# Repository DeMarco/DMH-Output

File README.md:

# DMH-Output
Kosmo format output module

## Features

### Line outputs and main volume

The L and R inputs accept the usual (Eurorack) modular synth audio amplitude of 10 V peak-to-peak.
The line level L and R outputs accept both balanced TRS and unbalanced TS cables.
The main volume control affects both L and R channels. The reduction factor can be set from from -infinite (silence) to -3 dB (max).
Since the usual 10 Vpp amplitude corresponds to around +13 dBu, this means the module can output from -infinite up to +10 dBu.
The precision dBu meter will max out at +6 dBu (red LED). Most professional audio equipment like mixers and audio interfaces expect a nominal input line level of +4 dBu.

### Headphone output

There's a separate stereo (TRS) headphone driving output with its own volume control, also with a range of -infinite to +10 dBu.
It can drive headphones with 32ohms or 85ohms with no problem. Higher impedances are also probably fine.

### External instrument inputs

The external inputs can amplify line level signals to the usual Eurorack amplitude of 10 Vpp with the help of a dedicated volume control. The input metering LEDs will turn yellow when the amplified signals at the Euro L and R outputs is between 9 and 11 Vpp, and red when above 11 Vpp.
This pre-amp has been designed with line level signals in mind, like those coming from another synthesizer or professional audio equipment. High impedance instrument outputs like electric guitars might not produce the best sound when connected directly to this module.

## Current consumption

+12V --> 110mA

-12V --> 110mA

## Dimensions

Height: 20cm

Width: 5cm

Depth: 5cm

## PCB set

- Front Panel
- Controls
- LEDs Aligner
- Main
- Mezzanine

## Gerbers

https://github.com/DeMarco/DMH-Output/tree/main/Gerbers

## Schematic and BoM

https://github.com/DeMarco/DMH-Output/blob/main/DMH_Output_Schematic.pdf

https://github.com/DeMarco/DMH-Output/blob/main/DMH_Output_BoM.csv

## Assembly and Calibration Instructions

https://github.com/DeMarco/DMH-Output/blob/main/Assembly_Instructions.md

## Font

For viewing/customizing in KiCad, I recommend downloading and installing the Nulshock font from Typodermic: https://typodermicfonts.com/nulshock/

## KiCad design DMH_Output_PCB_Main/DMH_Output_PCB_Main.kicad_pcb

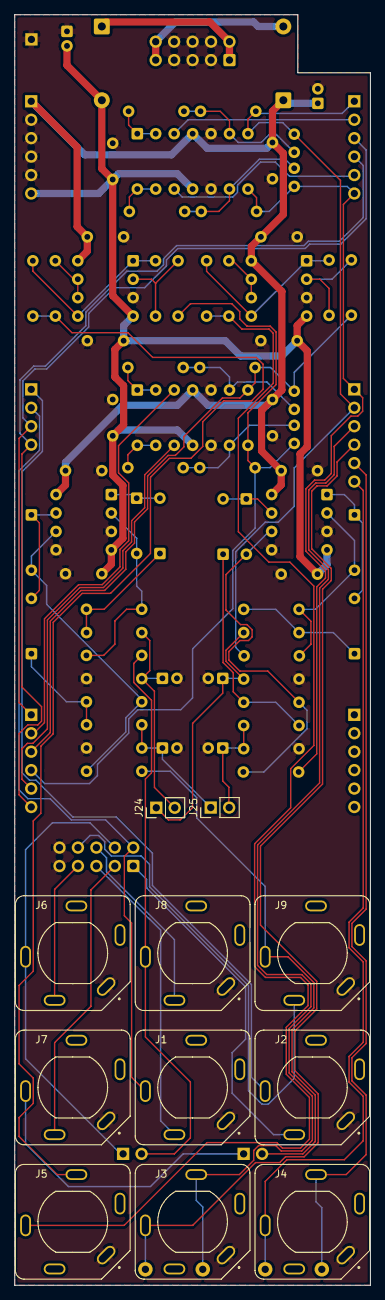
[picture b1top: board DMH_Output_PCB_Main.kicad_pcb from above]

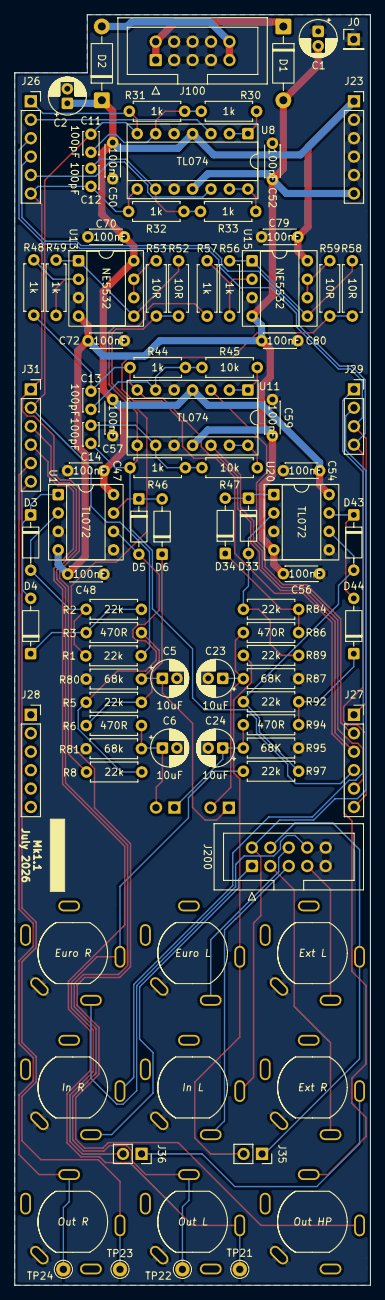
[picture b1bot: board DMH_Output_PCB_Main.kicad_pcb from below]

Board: 2 copper layers, 49.0 x 175.0 mm, 96 parts (85 on the bottom side), 63 nets.

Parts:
C1, C2: 47uF; CP_Radial_D5.0mm_P2.00mm
C5, C6, C23, C24: 10uF; CP_Radial_D5.0mm_P2.00mm
C11, C12, C13, C14: 100pF; C_Disc_D3.0mm_W2.0mm_P2.50mm
C47, C48, C50, C52, C54, C56, C57, C59, C70, C72, C79, C80: 100nF; C_Disc_D4.3mm_W1.9mm_P5.00mm
D1, D2: SB140; D_DO-41_SOD81_P10.16mm_Horizontal
D3, D4, D5, D6, D33, D34, D43, D44: 1N4148; D_DO-35_SOD27_P7.62mm_Horizontal
J0: Conn_01x01; PinHeader_1x01_P2.54mm_Vertical
J1, J2, J3, J4, J5, J6, J7, J8, J9: TRS_Jack_6.35mm_Sw; CUI_SJ-63083D
J23, J28: Conn_01x06; PinSocket_1x06_P2.54mm_Vertical
J24, J25: Conn_01x02; PinHeader_1x02_P2.54mm_Vertical
J26, J27, J31: Conn_01x06_PinHeader; PinSocket_1x06_P2.54mm_Vertical
J29: Conn_01x04_PinHeader; PinSocket_1x04_P2.54mm_Vertical
J35, J36: Conn_01x02_PinHeader; PinSocket_1x02_P2.54mm_Vertical
J100: IDC_02x05; IDC-Header_2x05_P2.54mm_Vertical_Eurorack
J200: IDC_02x05; IDC-Header_2x05_P2.54mm_Vertical_BackBone
R1, R2, R5, R8, R84, R89, R92, R97: 22k; R_Axial_DIN0207_L6.3mm_D2.5mm_P7.62mm_Horizontal
R3, R6, R86, R94: 470R; R_Axial_DIN0207_L6.3mm_D2.5mm_P7.62mm_Horizontal
R30, R31, R32, R33, R44, R46, R48, R49, R56, R57: 1k; R_Axial_DIN0207_L6.3mm_D2.5mm_P7.62mm_Horizontal
R45, R47: 10k; R_Axial_DIN0207_L6.3mm_D2.5mm_P7.62mm_Horizontal
R52, R53, R58, R59: 10R; R_Axial_DIN0207_L6.3mm_D2.5mm_P7.62mm_Horizontal
R80, R81: 68k; R_Axial_DIN0207_L6.3mm_D2.5mm_P7.62mm_Horizontal
R87, R95: 68K; R_Axial_DIN0207_L6.3mm_D2.5mm_P7.62mm_Horizontal
TP21, TP22, TP23, TP24: TestPoint; Pin_D1.0mm_L10.0mm
U1, U20: TL072; DIP-8_W7.62mm_Socket
U8, U11: TL074; DIP-14_W7.62mm_Socket
U13, U15: NE5532; DIP-8_W7.62mm_Socket

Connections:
+12V: C2.1, C47.1, C50.1, C54.1, C57.1, C70.1, C79.1, D2.1 (K), J23.1, U1.8 (V+), U8.4 (V+), U11.4 (V+), U13.8 (V+), U15.8 (V+), U20.8 (V+)
-12V: C1.2, C48.2, C52.2, C56.2, C59.2, C72.2, C80.2, D1.2 (A), J23.6, U1.4 (V-), U8.11 (V-), U11.11 (V-), U13.4 (V-), U15.4 (V-), U20.4 (V-)
/Balanced Line Driver/L_Bal_OUT_N_M: J3.R (4), J31.3, TP22.1 (1_1)
/Balanced Line Driver/L_Bal_OUT_P_M: J3.T (3), J31.4, TP21.1 (1_1)
/Balanced Line Driver/L_Ch_OUT_M: C11.2, J26.1, J31.2, R1.1, R31.2, U8.7
/Balanced Line Driver/R_Bal_OUT_N_M: J4.R (4), J31.5, TP24.1 (1_1)
/Balanced Line Driver/R_Bal_OUT_P_M: J4.T (3), J31.6, TP23.1 (1_1)
/Balanced Line Driver/R_Ch_OUT_M: C12.2, J26.6, J31.1, R8.1, R32.2, U8.8
/Gain Trimmer/L_Gain_IN_M: J26.3, J27.1, J29.3
/Gain Trimmer/R_Gain_IN_M: J26.4, J27.6, J29.4
/Headphone Amplifier/L_HP_OUT_M: J5.T (3), R52.2, R53.2
/Headphone Amplifier/R_HP_OUT_M: J5.R (4), R58.2, R59.2
/Input Meter/L_Ext_Meter_M: J8.T (3), J35.2, R89.1
/Input Meter/R_Ext_Meter_M: J9.T (3), J36.2, R97.1
/Pre-Gain Stage/L_In_M: J1.T (3), J29.2, J200.6
/Pre-Gain Stage/R_In_M: J2.T (3), J29.1
/PreAmp/L_Ext_IN_M: J6.T (3), J35.1, J200.7
/PreAmp/R_Ext_IN_M: J7.T (3), J36.1
GND: C1.1, C2.2, C5.2, C6.2, C23.2, C24.2, C47.2, C48.1, C50.2, C52.1, C54.2, C56.1, C57.2, C59.1, C70.2, C72.1, C79.2, C80.1, J0.1 (Pin_1_1), J1.S (1), J2.S (1), J3.S (1), J4.S (1), J5.S (1), J6.S (1), J7.S (1), J8.S (1), J9.S (1), J23.2, J23.3, J23.4, J23.5, J100.2a, J100.2b, J100.3a, J100.3b, J100.4a, J100.4b, J200.5, J200.10, R80.1, R81.1, R87.1, R95.1, U1.3 (+), U1.5 (+), U8.5 (+), U8.10 (+), U11.5 (+), U11.10 (+), U13.3 (+), U15.3 (+), U20.3 (+), U20.5 (+)
Input_Meter_L_M: C23.1, J24.2, R86.2, R87.2
Input_Meter_R_M: C24.1, J25.1, R94.2, R95.2
unnamed: D1.1 (K), J100.1a, J100.1b
unnamed: D2.2 (A), J100.5a, J100.5b
unnamed: D3.2 (A), R1.2, R2.1, U1.2 (-)
unnamed: D3.1 (K), D4.2 (A), U1.1
unnamed: D4.1 (K), R2.2, R3.1
unnamed: D5.2 (A), R5.1, R8.2, U1.6 (-)
unnamed: D5.1 (K), D6.2 (A), U1.7
unnamed: D6.1 (K), R5.2, R6.1
unnamed: D33.2 (A), R84.1, R89.2, U20.2 (-)
unnamed: D33.1 (K), D34.2 (A), U20.1
unnamed: D34.1 (K), R84.2, R86.1
unnamed: D43.2 (A), R92.1, R97.2, U20.6 (-)
unnamed: D43.1 (K), D44.2 (A), U20.7
unnamed: D44.1 (K), R92.2, R94.1
unnamed: J1.TN (2), J200.3
unnamed: J2.TN (2), J200.1
unnamed: J26.2, U8.3 (+)
unnamed: J26.5, U8.12 (+)
unnamed: J27.2, U11.3 (+)
unnamed: C13.2, J27.3, R44.2, R48.1, U11.7
unnamed: C14.2, J27.4, R46.2, R57.1, U11.8
unnamed: J27.5, U11.12 (+)
unnamed: J7.TN (2), J200.2
unnamed: J6.TN (2), J200.4
unnamed: J8.TN (2), J200.8
unnamed: J9.TN (2), J200.9
unnamed: R30.1, U8.1, U8.2 (-)
unnamed: C11.1, R30.2, R31.1, U8.6 (-)
unnamed: C12.1, R32.1, R33.2, U8.9 (-)
unnamed: R33.1, U8.13 (-), U8.14
unnamed: R45.1, U11.1, U11.2 (-)
unnamed: C13.1, R44.1, R45.2, U11.6 (-)
unnamed: C14.1, R46.1, R47.2, U11.9 (-)
unnamed: R47.1, U11.13 (-), U11.14
unnamed: R48.2, R49.1, U13.2 (-)
unnamed: R49.2, R52.1, U13.1, U13.5 (+)
unnamed: R53.1, U13.6 (-), U13.7
unnamed: R56.1, R57.2, U15.2 (-)
unnamed: R56.2, R58.1, U15.1, U15.5 (+)
unnamed: R59.1, U15.6 (-), U15.7
Output_Meter_L_M: C5.1, J24.1, R3.2, R80.2
Output_Meter_R_M: C6.1, J25.2, R6.2, R81.2

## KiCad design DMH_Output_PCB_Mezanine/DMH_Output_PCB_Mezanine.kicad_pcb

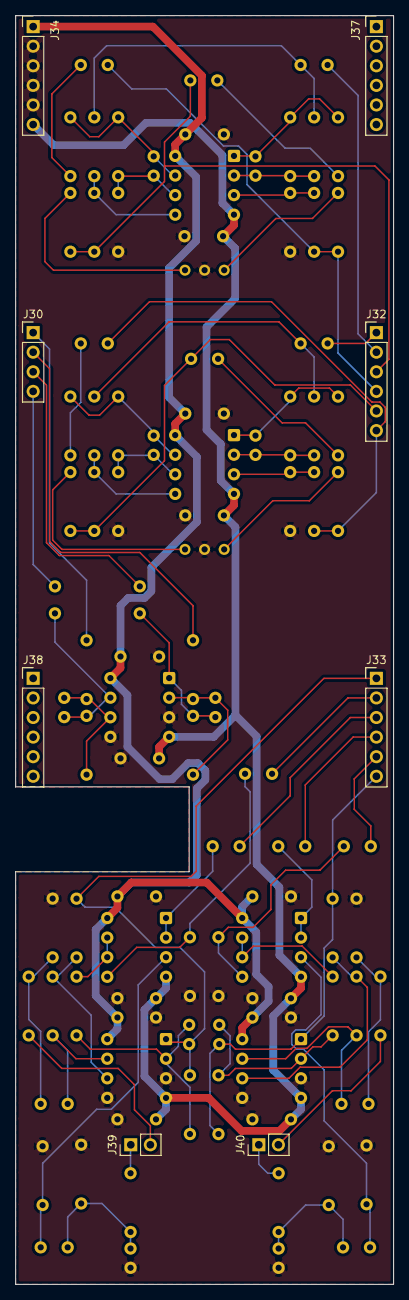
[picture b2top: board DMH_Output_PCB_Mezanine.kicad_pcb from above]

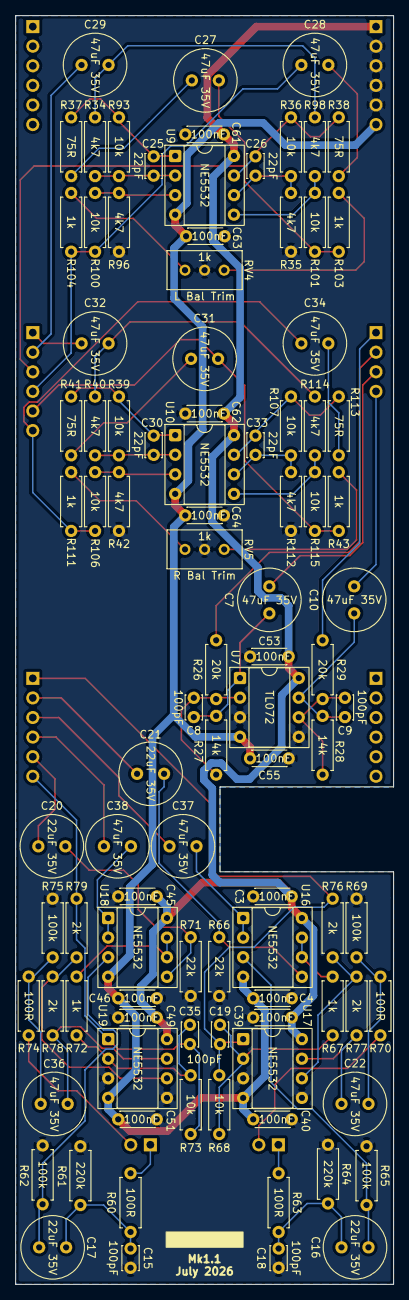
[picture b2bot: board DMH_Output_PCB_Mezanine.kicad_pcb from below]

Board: 2 copper layers, 49.0 x 164.5 mm, 105 parts (97 on the bottom side), 67 nets.

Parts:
C3, C4, C39, C40, C45, C46, C49, C51, C53, C55, C61, C62, C63, C64: 100nF; C_Disc_D4.3mm_W1.9mm_P5.00mm
C7, C10, C22, C27, C28, C29, C31, C32, C34, C36, C37, C38: 47uF 35V; C_Radial_D8.0mm_H11.5mm_P3.50mm
C8, C9, C15, C18, C19, C35: 100pF; C_Disc_D3.0mm_W2.0mm_P2.50mm
C16, C17, C20, C21: 22uF 35V; C_Radial_D8.0mm_H11.5mm_P3.50mm
C25, C26, C30, C33: 22pF; C_Disc_D3.0mm_W2.0mm_P2.50mm
J30: Conn_01x04_PinHeader; PinHeader_1x04_P2.54mm_Vertical
J32: Conn_01x06_PinHeader; PinHeader_1x06_P2.54mm_Vertical
J33, J34, J37, J38: Conn_01x06; PinHeader_1x06_P2.54mm_Vertical
J39, J40: Conn_01x02_PinHeader; PinHeader_1x02_P2.54mm_Vertical
R26, R29: 20k; R_Axial_DIN0207_L6.3mm_D2.5mm_P7.62mm_Horizontal
R27, R28: 14k; R_Axial_DIN0207_L6.3mm_D2.5mm_P7.62mm_Horizontal
R34, R35, R40, R42, R96, R98, R112, R114: 4k7; R_Axial_DIN0207_L6.3mm_D2.5mm_P7.62mm_Horizontal
R36, R39, R68, R73, R93, R100, R101, R106, R107, R115: 10k; R_Axial_DIN0207_L6.3mm_D2.5mm_P7.62mm_Horizontal
R37, R38, R41, R113: 75R; R_Axial_DIN0207_L6.3mm_D2.5mm_P7.62mm_Horizontal
R43, R67, R72, R103, R104, R111: 1k; R_Axial_DIN0207_L6.3mm_D2.5mm_P7.62mm_Horizontal
R60, R63, R70, R74: 100R; R_Axial_DIN0207_L6.3mm_D2.5mm_P7.62mm_Horizontal
R61, R64: 220k; R_Axial_DIN0207_L6.3mm_D2.5mm_P7.62mm_Horizontal
R62, R65, R69, R75: 100k; R_Axial_DIN0207_L6.3mm_D2.5mm_P7.62mm_Horizontal
R66, R71: 22k; R_Axial_DIN0207_L6.3mm_D2.5mm_P7.62mm_Horizontal
R76, R77, R78, R79: 2k; R_Axial_DIN0207_L6.3mm_D2.5mm_P7.62mm_Horizontal
RV4, RV5: 1k; Potentiometer_Bourns_3296W_Vertical
U7: TL072; DIP-8_W7.62mm_Socket
U9, U10, U16, U17, U18, U19: NE5532; DIP-8_W7.62mm_Socket

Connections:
+12V: C3.1, C39.1, C45.1, C49.1, C53.1, C61.1, C62.1, J34.1, U7.8 (V+), U9.8 (V+), U10.8 (V+), U16.8 (V+), U17.8 (V+), U18.8 (V+), U19.8 (V+)
-12V: C4.2, C40.2, C46.2, C51.2, C55.2, C63.2, C64.2, J34.6, U7.4 (V-), U9.4 (V-), U10.4 (V-), U16.4 (V-), U17.4 (V-), U18.4 (V-), U19.4 (V-)
/PreAmp/RV3A_p1_MZ: C19.2, J33.1, R68.2, R76.1, U17.1
/PreAmp/RV3A_p2_MZ: C21.2, J33.2
/PreAmp/RV3A_p3_MZ: C37.2, J33.3
/PreAmp/RV3B_p4_MZ: C35.2, J33.6, R73.2, R79.1, U19.1
/PreAmp/RV3B_p5_MZ: C20.2, J33.5
/PreAmp/RV3B_p6_MZ: C38.2, J33.4
GND: C3.2, C4.1, C15.1, C18.1, C39.2, C40.1, C45.2, C46.1, C49.2, C51.1, C53.2, C55.1, C61.2, C62.2, C63.1, C64.1, J34.2, J34.3, J34.4, J34.5, R35.1, R42.1, R61.1, R62.1, R64.1, R65.1, R66.1, R69.1, R71.1, R75.1, R96.1, R112.1, RV4.2, RV5.2, U7.3 (+), U7.5 (+), U17.3 (+), U17.5 (+), U19.3 (+), U19.5 (+)
unnamed: C7.1, C8.2, R27.2, U7.1
unnamed: C9.2, C10.1, R28.2, U7.7
unnamed: C15.2, C17.1, R60.2, R61.2
unnamed: C16.1, C18.2, R63.2, R64.2
unnamed: C22.1, R77.2, U17.7
unnamed: C22.2, R69.2, R70.1
unnamed: C25.2, R37.1, R93.2, U9.1
unnamed: C26.2, R36.2, R38.1, U9.7
unnamed: C27.1, R37.2
unnamed: C28.1, R38.2
unnamed: C29.2, R34.1, R98.1
unnamed: C30.2, R39.2, R41.1, U10.1
unnamed: C31.1, R41.2
unnamed: C32.2, R40.1, R114.1
unnamed: C33.2, R107.2, R113.1, U10.7
unnamed: C34.1, R113.2
unnamed: C36.1, R78.2, U19.7
unnamed: C36.2, R74.1, R75.2
unnamed: J30.1, R29.1
unnamed: J30.2, R26.1
unnamed: C7.2, J30.3
unnamed: C10.2, J30.4
unnamed: C32.1, J32.1
unnamed: C29.1, J32.2
unnamed: C27.2, J32.3, R101.2, R103.2
unnamed: C28.2, J32.4, R100.2, R104.1
unnamed: C31.2, J32.5, R43.2, R115.2
unnamed: C34.2, J32.6, R106.2, R111.1
unnamed: J39.1, R63.1
unnamed: J39.2, R70.2
unnamed: J40.1, R60.1
unnamed: J40.2, R74.2
unnamed: R43.1, RV5.3
unnamed: R103.1, RV4.3
unnamed: R104.2, RV4.1
unnamed: R111.2, RV5.1
unnamed: C8.1, R26.2, R27.1, U7.2 (-)
unnamed: C9.1, R28.1, R29.2, U7.6 (-)
unnamed: R96.2, R100.1, U9.3 (+)
unnamed: C25.1, R34.2, R93.1, U9.2 (-)
unnamed: R98.2, R101.1, U9.5 (+)
unnamed: C26.1, R35.2, R36.1, U9.6 (-)
unnamed: R42.2, R106.1, U10.3 (+)
unnamed: C30.1, R39.1, R40.2, U10.2 (-)
unnamed: R114.2, R115.1, U10.5 (+)
unnamed: C33.1, R107.1, R112.2, U10.6 (-)
unnamed: C16.2, R65.2, U16.3 (+)
unnamed: C37.1, U16.1, U16.2 (-)
unnamed: C21.1, R66.2, U16.5 (+)
unnamed: R67.1, U16.6 (-), U16.7
unnamed: C19.1, R67.2, R68.1, U17.2 (-)
unnamed: R76.2, R77.1, U17.6 (-)
unnamed: C17.2, R62.2, U18.3 (+)
unnamed: C38.1, U18.1, U18.2 (-)
unnamed: C20.1, R71.2, U18.5 (+)
unnamed: R72.1, U18.6 (-), U18.7
unnamed: C35.1, R72.2, R73.1, U19.2 (-)
unnamed: R78.1, R79.2, U19.6 (-)

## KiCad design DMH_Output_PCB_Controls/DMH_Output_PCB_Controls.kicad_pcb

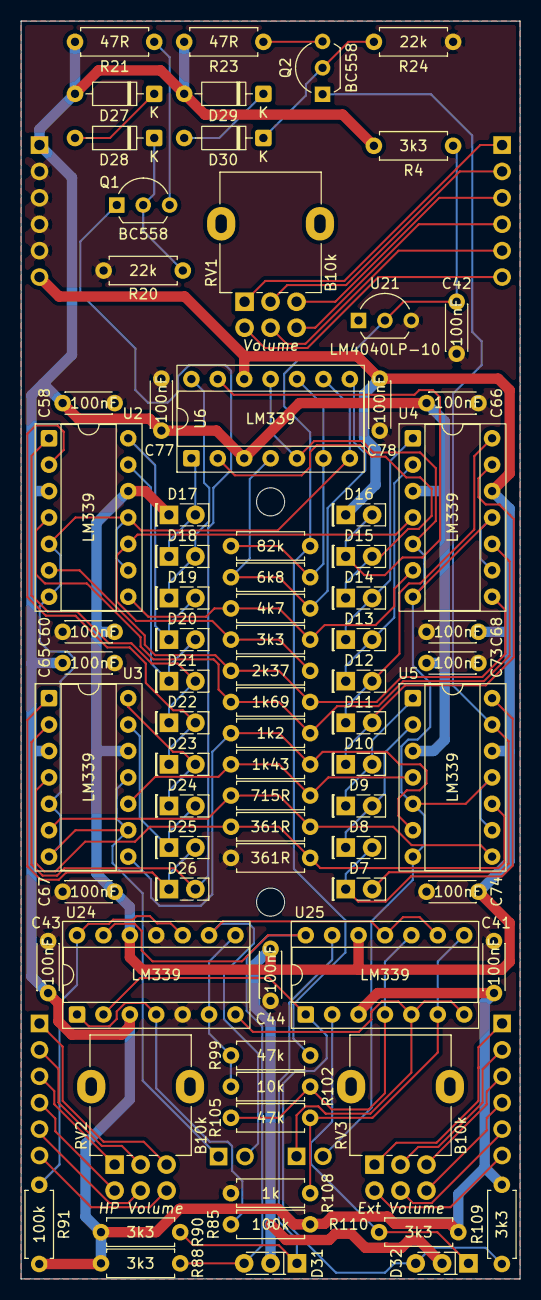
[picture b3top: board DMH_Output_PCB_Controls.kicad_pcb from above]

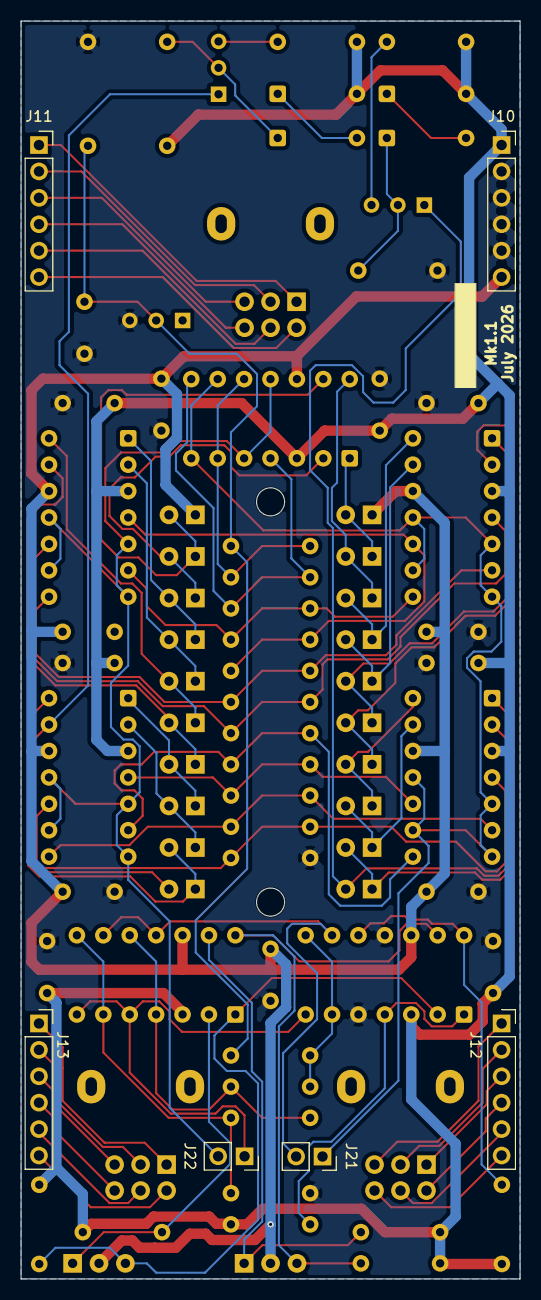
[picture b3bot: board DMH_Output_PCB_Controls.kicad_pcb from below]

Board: 2 copper layers, 48.0 x 121.0 mm, 87 parts (6 on the bottom side), 71 nets.

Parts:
C41, C42, C43, C44, C58, C60, C65, C66, C67, C68, C73, C74, C77, C78: 100nF; C_Disc_D4.3mm_W1.9mm_P5.00mm
D7, D8, D9, D10, D11, D12, D13, D20, D21, D22, D23, D24, D25, D26: LED_G; LED_Rectangular_W5.0mm_H2.0mm
D14, D15, D18, D19: LED_Y; LED_Rectangular_W5.0mm_H2.0mm
D16, D17: LED_R; LED_Rectangular_W5.0mm_H2.0mm
D27, D28, D29, D30: 1N4148; D_DO-35_SOD27_P7.62mm_Horizontal
D31, D32: LED_Dual_AKA; LED_Rectangular_W5.0mm_H2.0mm-3Pins
H21, H22: MountingHole; MountingHole_2.7mm_M2.5_ISO14580
J10, J13: Conn_01x06; PinSocket_1x06_P2.54mm_Vertical
J11, J12: Conn_01x06_PinHeader; PinSocket_1x06_P2.54mm_Vertical
J21, J22: Conn_01x02; PinSocket_1x02_P2.54mm_Vertical
Q1, Q2: BC558; TO-92L_Inline_Wide
R4, R12, R88, R90, R109, R110: 3k3; R_Axial_DIN0207_L6.3mm_D2.5mm_P7.62mm_Horizontal
R9: 82k; R_Axial_DIN0207_L6.3mm_D2.5mm_P7.62mm_Horizontal
R10: 6k8; R_Axial_DIN0207_L6.3mm_D2.5mm_P7.62mm_Horizontal
R11: 4k7; R_Axial_DIN0207_L6.3mm_D2.5mm_P7.62mm_Horizontal
R13: 2k37; R_Axial_DIN0207_L6.3mm_D2.5mm_P7.62mm_Horizontal
R14: 1k69; R_Axial_DIN0207_L6.3mm_D2.5mm_P7.62mm_Horizontal
R15: 1k2; R_Axial_DIN0207_L6.3mm_D2.5mm_P7.62mm_Horizontal
R16: 1k43; R_Axial_DIN0207_L6.3mm_D2.5mm_P7.62mm_Horizontal
R17: 715R; R_Axial_DIN0207_L6.3mm_D2.5mm_P7.62mm_Horizontal
R18, R19: 361R; R_Axial_DIN0207_L6.3mm_D2.5mm_P7.62mm_Horizontal
R20, R24: 22k; R_Axial_DIN0207_L6.3mm_D2.5mm_P7.62mm_Horizontal
R21, R23: 47R; R_Axial_DIN0207_L6.3mm_D2.5mm_P7.62mm_Horizontal
R85, R91: 100k; R_Axial_DIN0207_L6.3mm_D2.5mm_P7.62mm_Horizontal
R99, R105: 47k; R_Axial_DIN0207_L6.3mm_D2.5mm_P7.62mm_Horizontal
R102: 10k; R_Axial_DIN0207_L6.3mm_D2.5mm_P7.62mm_Horizontal
R108: 1k; R_Axial_DIN0207_L6.3mm_D2.5mm_P7.62mm_Horizontal
RV1, RV2, RV3: B10k; Potentiometer_Alpha_RD902F-40-00D_Dual_Vertical
U2, U3, U4, U5, U6, U24, U25: LM339; DIP-14_W7.62mm_Socket
U21: LM4040LP-10; TO-92L_Inline_Wide

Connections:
+10V: C42.1, R4.1, R9.2, R99.2, U21.2 (K)
+12V: C41.1, C43.1, C58.1, C65.1, C66.1, C73.1, C77.1, D27.2 (A), D29.2 (A), J10.1, R4.2, R21.2, R23.2, R85.2, R88.2, R90.2, R91.2, R109.2, R110.2, U2.3 (V+), U3.3 (V+), U4.3 (V+), U5.3 (V+), U6.3 (V+), U24.3 (V+), U25.3 (V+)
-12V: C44.2, C60.2, C67.2, C68.2, C74.2, C78.2, D16.1 (K), D17.1 (K), D31.2 (K), D32.2 (K), J10.6, U2.12 (V-), U3.12 (V-), U4.12 (V-), U5.12 (V-), U6.12 (V-), U24.12 (V-), U25.12 (V-)
/PreAmp/RV3A_p1_C: J13.1, RV3.1
/PreAmp/RV3A_p2_C: J13.2, RV3.2
/PreAmp/RV3A_p3_C: J13.3, RV3.3
/PreAmp/RV3B_p4_C: J13.6, RV3.4
/PreAmp/RV3B_p5_C: J13.5, RV3.5
/PreAmp/RV3B_p6_C: J13.4, RV3.6
GND: C41.2, C42.2, C43.2, C44.1, C58.2, C60.1, C65.2, C66.2, C67.1, C68.1, C73.2, C74.1, C77.2, C78.1, J10.2, J10.3, J10.4, J10.5, R19.1, R20.1, R24.1, R108.1, U21.3 (A), U24.5 (+), U24.11 (+)
Input_Meter_L_C: J21.2, U24.9 (+), U25.9 (+), U25.11 (+)
Input_Meter_R_C: J22.1, U24.7 (+), U25.5 (+), U25.7 (+)
unnamed: D7.2 (A), Q2.1 (C), U5.13
unnamed: D7.1 (K), D8.2 (A), U5.14
unnamed: D8.1 (K), D9.2 (A), U5.2
unnamed: D9.1 (K), D10.2 (A), U5.1
unnamed: D10.1 (K), D11.2 (A), U4.13
unnamed: D11.1 (K), D12.2 (A), U4.14
unnamed: D12.1 (K), D13.2 (A), U4.2
unnamed: D13.1 (K), D14.2 (A), U4.1
unnamed: D14.1 (K), D15.2 (A), U6.2
unnamed: D15.1 (K), D16.2 (A), U6.13
unnamed: D17.2 (A), D18.1 (K), U6.1
unnamed: D18.2 (A), D19.1 (K), U6.14
unnamed: D19.2 (A), D20.1 (K), U2.14
unnamed: D20.2 (A), D21.1 (K), U2.13
unnamed: D21.2 (A), D22.1 (K), U2.1
unnamed: D22.2 (A), D23.1 (K), U2.2
unnamed: D23.2 (A), D24.1 (K), U3.14
unnamed: D24.2 (A), D25.1 (K), U3.13
unnamed: D25.2 (A), D26.1 (K), U3.1
unnamed: D26.2 (A), Q1.1 (C), U3.2
unnamed: D27.1 (K), D28.2 (A)
unnamed: D28.1 (K), Q1.2 (B), R20.2
unnamed: D29.1 (K), D30.2 (A)
unnamed: D30.1 (K), Q2.2 (B), R24.2
unnamed: D31.1 (A1), R90.1, U25.13
unnamed: D31.3 (A2), R88.1, U24.13, U25.14
unnamed: D32.1 (A1), R110.1, U25.2
unnamed: D32.3 (A2), R109.1, U24.2, U25.1
unnamed: J11.1, RV1.1
unnamed: J11.2, RV1.2
unnamed: J11.3, RV1.3
unnamed: J11.4, RV1.6
unnamed: J11.5, RV1.5
unnamed: J11.6, RV1.4
unnamed: J12.1, RV2.3
unnamed: J12.2, RV2.2
unnamed: J12.3, RV2.1
unnamed: J12.4, RV2.4
unnamed: J12.5, RV2.5
unnamed: J12.6, RV2.6
unnamed: Q1.3 (E), R21.1
unnamed: Q2.3 (E), R23.1
unnamed: R14.1, R15.2, U2.4 (-), U4.10 (-)
unnamed: R13.1, R14.2, U2.6 (-), U4.8 (-)
unnamed: R12.1, R13.2, U2.10 (-), U4.4 (-)
unnamed: R11.1, R12.2, U2.8 (-), U4.6 (-)
unnamed: R18.1, R19.2, U3.4 (-), U5.10 (-)
unnamed: R17.1, R18.2, U3.6 (-), U5.8 (-)
unnamed: R16.1, R17.2, U3.10 (-), U5.4 (-)
unnamed: R15.1, R16.2, U3.8 (-), U5.6 (-)
unnamed: R10.1, R11.2, U6.4 (-), U6.8 (-)
unnamed: R9.1, R10.2, U6.6 (-), U6.10 (-)
unnamed: R85.1, U24.1, U24.4 (-)
unnamed: R99.1, R102.2, U24.6 (-), U24.8 (-)
unnamed: R91.1, U24.10 (-), U24.14
unnamed: R102.1, R105.2, U25.4 (-), U25.10 (-)
unnamed: R105.1, R108.2, U25.6 (-), U25.8 (-)
Output_Meter_L_C: J21.1, U2.5 (+), U2.7 (+), U2.9 (+), U2.11 (+), U3.5 (+), U3.7 (+), U3.9 (+), U3.11 (+), U6.7 (+), U6.9 (+)
Output_Meter_R_C: J22.2, U4.5 (+), U4.7 (+), U4.9 (+), U4.11 (+), U5.5 (+), U5.7 (+), U5.9 (+), U5.11 (+), U6.5 (+), U6.11 (+)

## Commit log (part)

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2025-10-16 Created panel project
2025-10-16 Panel design in progress
2025-10-16 Front panel design in progress
2025-10-17 Designed front panel
2025-10-17 Finished front panel design
2025-11-23 Created PCB 1 project
2025-12-04 Schematic in progress
2025-12-06 PreAmp design starting
2025-12-06 Designed preamp circuit
2025-12-07 Simulating signal detector
2025-12-07 Simulating signal and peak detection
2025-12-12 Designed external input meter
2025-12-14 Changed balanced output for quasi-floating design
2025-12-14 Redesigned external input preamp
2025-12-17 Updated output meter peak detectors
2025-12-17 Adjusted gains
2025-12-19 Updated meters resistor values
2025-12-20 Exported preliminary BoM
2025-12-22 Linked TRS jacks footprint
2026-02-22 Centralized library
2026-02-22 Adjustments during breadboarding
2026-03-03 Starting design of Controls PCB
2026-03-04 Simulated 10V ref for VU meter
2026-03-07 Adjusted meter circuits
2026-03-07 Starting Controls PCB design
2026-03-07 Controls PCB placement ongoing
2026-03-08 Controls PCB placement in progress
2026-03-08 Controls PCB comp placement done
2026-03-08 Re-arranged LM339 connections
2026-03-09 Controls PCB routing ongoing
2026-03-09 Clarifying inter PCB connectors in progress
2026-03-09 Clarified interPCB connectors in schematic
2026-03-09 Controls PCB routing in progress
2026-03-09 Controls PCB Routing done
2026-03-10 Created LEDs baffle PCB
2026-03-10 Created Main PCB project
2026-03-10 Preparing for L and R submodule split
2026-03-10 Preparing for split in submodules
2026-03-10 Generated Gerbers for prototyping
    Panel, Controls and LEDs only
2026-03-17 Regenerated LEDs baffle Gerbers
    Added second GND plated hole to avoid issues with the probe test at JLC
2026-03-26 Adjustments during prototyping
2026-03-31 Update SynthStuff
2026-04-25 Removed 2 extra OpAmps from the headphone amp
2026-04-26 Changed headphone amp max gain
2026-04-27 Replaced jack symbols with 5pin ones
    Also updated Meter LED current source resistor to 75R
    Also increased LED guiding PCB mounting holes to M2.5
2026-05-02 Prep for Main and MZ PCBs design in progress
2026-05-02 Prepped for Main PCB design
2026-05-02 Prepped for Main PCB comp placement
2026-05-02 Placed pin sockets
2026-05-03 Main PCB comp placement in progress
2026-05-03 PCB Main comp placement done
2026-05-03 Main PCB routing in progress
2026-05-04 Main PCB routing done
2026-05-04 Started Mezanine PCB project
2026-05-04 Defined Mezanine PCB outer limits
2026-05-07 Placed PreAmp components on PCB
2026-05-10 Placed pre-gain stage components
2026-05-10 Mezanine PCB comp placement done
2026-05-10 routing ongoing
2026-05-11 routing in progress
2026-05-13 Mezanine PCB routing done
2026-06-24 Moved PCB_1 to old versions folder
2026-06-25 Re-exported all Gerbers
